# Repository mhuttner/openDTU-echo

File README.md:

# openDTU Echo

PCB for openDTU onBattery

This PCB can be easily ordered from JLCPCB with assembly, but the ESP32-S3 and the Ebyte E49-900M20S module need to be soldered by hand.

## Features

- ESP32-S3
- CMT2300A Chip in an Ebyte E49-900M20S module, NRF Chip is **not** supported
- Three ADUM1201 isolators with Ports for Victron VE.Direct Charge controllers / Smart Shunt
- SN65HVD230 CAN transceiver connected to RJ45 connector (Pin 4 and 5)
- ISL3178EIBZ RS485 transceiver connected to RJ45 connector (Pin 1 and 2)
- 3.3V Switching regulator based on the TPS54202DDC
- I2C Header for an OLED display

## Schematic

## PCB

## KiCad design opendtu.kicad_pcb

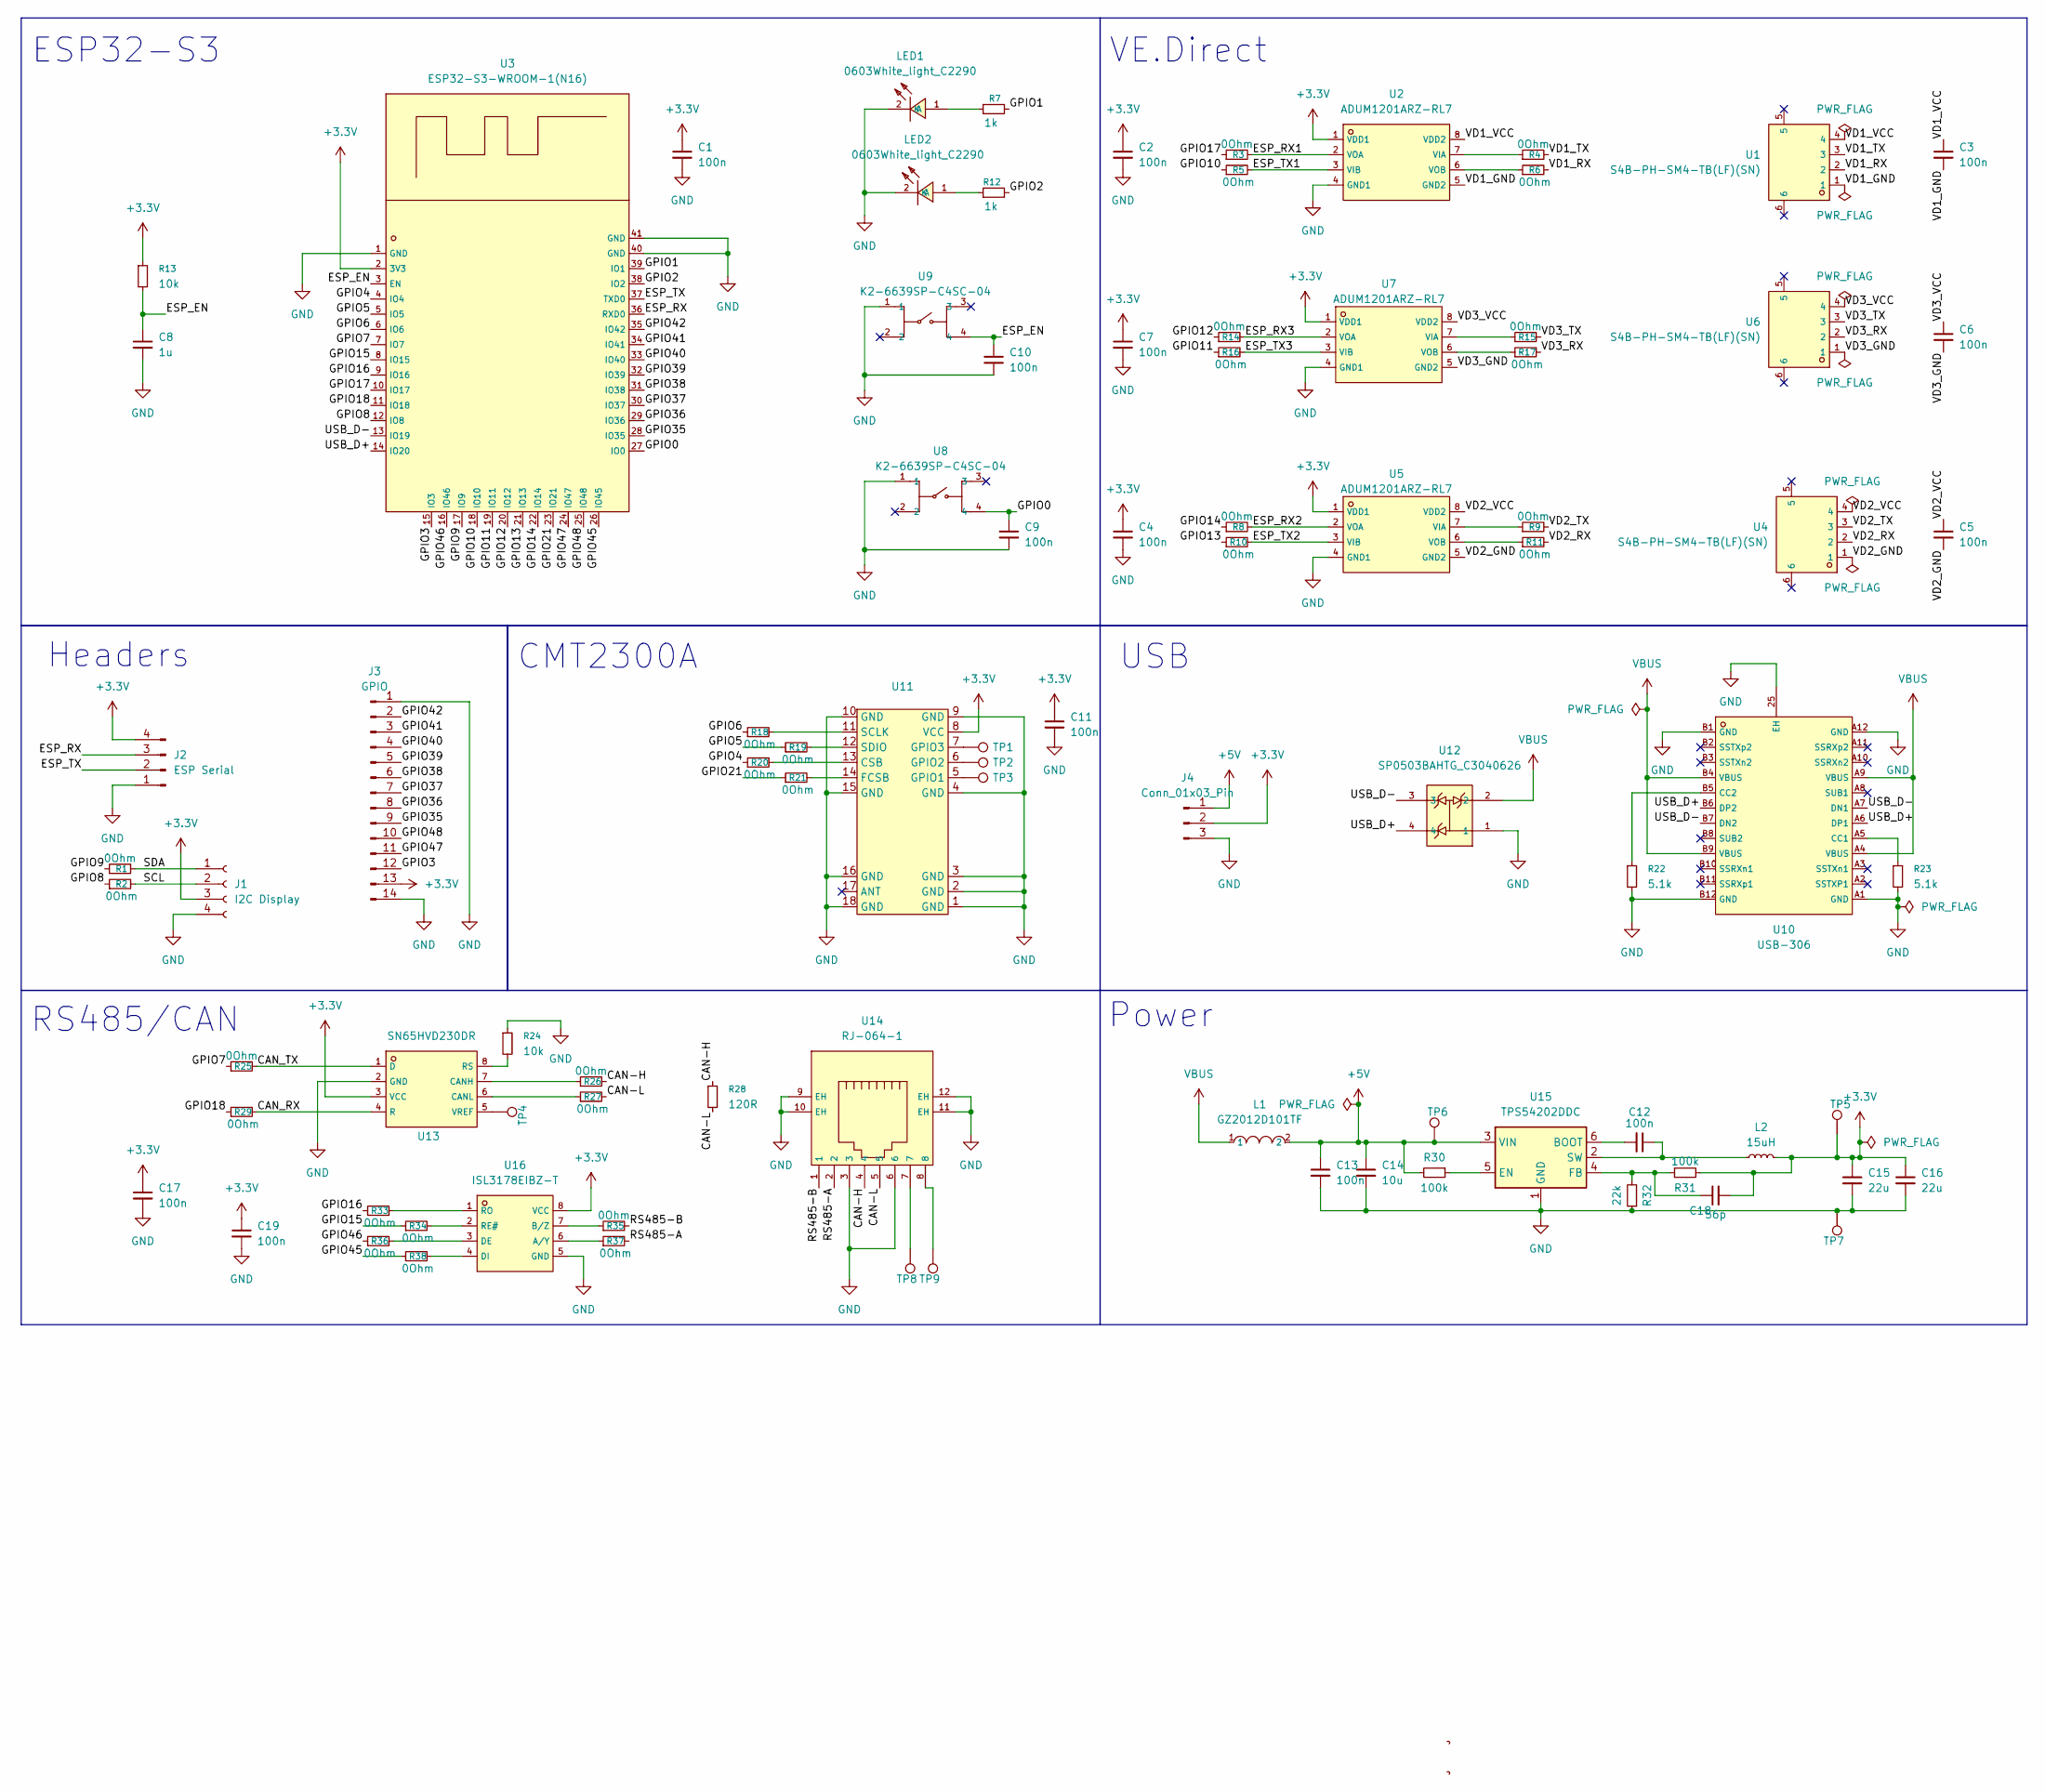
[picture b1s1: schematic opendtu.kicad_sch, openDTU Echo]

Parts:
C1, C2, C3, C4, C5, C6, C7, C9, C10, C11, C12, C17, C19: 100n; C_0402_1005Metric
C8: 1u; C_0603_1608Metric
C13: 100n; C_0603_1608Metric
C14: 10u; C_0603_1608Metric
C15, C16: 22u; C_1206_3216Metric
C18: 56p; C_0603_1608Metric
J1: I2C Display; PinSocket_1x04_P2.54mm_Vertical
J2: ESP Serial; PinHeader_1x04_P2.54mm_Vertical
J3: GPIO; PinHeader_1x14_P2.54mm_Vertical
J4: Conn_01x03_Pin; PinHeader_1x03_P2.54mm_Vertical
L1: GZ2012D101TF; L0805; LCSC C1015
L2: 15uH; IND-SMD_L7.1-W6.6_SLO0618H
LED1, LED2: 0603White_light_C2290; LED0603-R-RD_WHITE; LCSC C2290
R1, R2, R3, R4, R5, R6, R8, R9, R10, R11, R14, R15, R16, R17, R18, R19, R20, R21, R25, R26, R27, R29, R33, R34, R35, R36, R37, R38: 0Ohm; R_0805_2012Metric
R7, R12: 1k; R_0603_1608Metric
R13: 10k; C_0805_2012Metric
R22, R23: 5.1k; R_0805_2012Metric
R24: 10k; R_0805_2012Metric
R28: 120R; R_0805_2012Metric
R30, R31: 100k; R_0805_2012Metric
R32: 22k; R_0805_2012Metric
TP1, TP2, TP3, TP4, TP5, TP6, TP7, TP8, TP9: TestPoint; TestPoint_Pad_D2.0mm
U1, U4, U6: S4B-PH-SM4-TB(LF)(SN); CONN-SMD_S4B-PH-SM4-TB-LF-SN; LCSC C265102
U2, U5, U7: ADUM1201ARZ-RL7; SOIC-8_L4.9-W3.9-P1.27-LS6.0-BL; LCSC C9669
U3: ESP32-S3-WROOM-1(N16); WIRELM-SMD_ESP32-S3-WROOM-1; LCSC C2913199
U8, U9: K2-6639SP-C4SC-04; KEY-SMD_4P-L6.0-W6.0-P3.90-LS9.0; LCSC C83206
U10: USB-306; USB-TYPE-C-TH_USB-306.; LCSC C309338
U11: E49-900M20S
U12: SP0503BAHTG_C3040626; SOT-143-4_L2.9-W1.3-P1.92-LS2.4-BL; LCSC C3040626
U13: SN65HVD230DR; SOIC-8_L4.9-W3.9-P1.27-LS6.0-BL; LCSC C12084
U14: RJ-064-1; CONN-SMD_RJ-064; LCSC C7205199
U15: TPS54202DDC; SOT-23-6
U16: ISL3178EIBZ-T; SOIC-8_L4.9-W3.9-P1.27-LS6.0-BL; LCSC C382015

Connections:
+3.3V: C1.1, C2.1, C4.1, C7.1, C11.1, C15.1, C16.1, C17.1, C18.2, C19.1, J1.3, J2.4, J3.13, J4.2, L2.2, R13.1, R31.2, TP5.1, U2.1 (VDD1), U3.2 (3V3), U5.1 (VDD1), U7.1 (VDD1), U11.8 (VCC), U13.3 (VCC), U16.8 (VCC)
+5V: C13.1, C14.1, J4.1, L1.2, R30.2, TP6.1, U15.3 (VIN)
/CAN-H: R26.2, R28.1, U14.4
/CAN-L: R27.2, R28.2, U14.5
/CAN_RX: R29.2, U13.4 (R)
/CAN_TX: R25.2, U13.1 (D)
/ESP_EN: C8.1, C10.1, R13.2, U3.3 (EN), U9.4
/ESP_RX: J2.3, U3.36 (RXD0)
/ESP_RX1: R3.2, U2.2 (VOA)
/ESP_RX2: R8.2, U5.2 (VOA)
/ESP_RX3: R14.2, U7.2 (VOA)
/ESP_TX: J2.2, U3.37 (TXD0)
/ESP_TX1: R5.2, U2.3 (VIB)
/ESP_TX2: R10.2, U5.3 (VIB)
/ESP_TX3: R16.2, U7.3 (VIB)
/GPIO0: C9.1, U3.27 (IO0), U8.4
/GPIO1: R7.2, U3.39 (IO1)
/GPIO2: R12.2, U3.38 (IO2)
/GPIO3: J3.12, U3.15 (IO3)
/GPIO4: R20.1, U3.4 (IO4)
/GPIO5: R19.1, U3.5 (IO5)
/GPIO6: R18.1, U3.6 (IO6)
/GPIO7: R25.1, U3.7 (IO7)
/GPIO8: R2.1, U3.12 (IO8)
/GPIO9: R1.1, U3.17 (IO9)
/GPIO10: R5.1, U3.18 (IO10)
/GPIO11: R16.1, U3.19 (IO11)
/GPIO12: R14.1, U3.20 (IO12)
/GPIO13: R10.1, U3.21 (IO13)
/GPIO14: R8.1, U3.22 (IO14)
/GPIO15: R34.1, U3.8 (IO15)
/GPIO16: R33.1, U3.9 (IO16)
/GPIO17: R3.1, U3.10 (IO17)
/GPIO18: R29.1, U3.11 (IO18)
/GPIO21: R21.1, U3.23 (IO21)
/GPIO35: J3.9, U3.28 (IO35)
/GPIO36: J3.8, U3.29 (IO36)
/GPIO37: J3.7, U3.30 (IO37)
/GPIO38: J3.6, U3.31 (IO38)
/GPIO39: J3.5, U3.32 (IO39)
/GPIO40: J3.4, U3.33 (IO40)
/GPIO41: J3.3, U3.34 (IO41)
/GPIO42: J3.2, U3.35 (IO42)
/GPIO45: R38.1, U3.26 (IO45)
/GPIO46: R36.1, U3.16 (IO46)
/GPIO47: J3.11, U3.24 (IO47)
/GPIO48: J3.10, U3.25 (IO48)
/RS485-A: R37.2, U14.2
/RS485-B: R35.2, U14.1
/SCL: J1.2, R2.2
/SDA: J1.1, R1.2
/USB_D+: U3.14 (IO20), U10.A6 (DP1), U10.B6 (DP2), U12.4
/USB_D-: U3.13 (IO19), U10.A7 (DN1), U10.B7 (DN2), U12.3
/VD1_GND: C3.2, U1.1, U2.5 (GND2)
/VD1_RX: R6.2, U1.2
/VD1_TX: R4.2, U1.3
/VD1_VCC: C3.1, U1.4, U2.8 (VDD2)
/VD2_GND: C5.2, U4.1, U5.5 (GND2)
/VD2_RX: R11.2, U4.2
/VD2_TX: R9.2, U4.3
/VD2_VCC: C5.1, U4.4, U5.8 (VDD2)
/VD3_GND: C6.2, U6.1, U7.5 (GND2)
/VD3_RX: R17.2, U6.2
/VD3_TX: R15.2, U6.3
/VD3_VCC: C6.1, U6.4, U7.8 (VDD2)
GND: C1.2, C2.2, C4.2, C7.2, C8.2, C9.2, C10.2, C11.2, C13.2, C14.2, C15.2, C16.2, C17.2, C19.2, J1.4, J2.1, J3.1, J3.14, J4.3, LED1.2 (K), LED2.2 (K), R22.2, R23.2, R24.1, R32.1, TP7.1, U2.4 (GND1), U3.1 (GND), U3.40 (GND), U3.41 (GND), U5.4 (GND1), U7.4 (GND1), U8.1, U9.1, U10.25 (EH), U10.A1 (GND), U10.A12 (GND), U10.B1 (GND), U10.B12 (GND), U11.1 (GND), U11.2 (GND), U11.3 (GND), U11.4 (GND), U11.9 (GND), U11.10 (GND), U11.15 (GND), U11.16 (GND), U11.18 (GND), U12.1, U13.2 (GND), U14.3, U14.6, U14.9 (EH), U14.10 (EH), U14.11 (EH), U14.12 (EH), U15.1 (GND), U16.5 (GND)
unnamed: LED1.1 (A), R7.1
unnamed: LED2.1 (A), R12.1
unnamed: TP8.1, U14.7
unnamed: TP9.1, U14.8
unnamed: R4.1, U2.7 (VIA)
unnamed: R6.1, U2.6 (VOB)
unnamed: R9.1, U5.7 (VIA)
unnamed: R11.1, U5.6 (VOB)
unnamed: R15.1, U7.7 (VIA)
unnamed: R17.1, U7.6 (VOB)
unnamed: R23.1, U10.A5 (CC1)
unnamed: R22.1, U10.B5 (CC2)
unnamed: R20.2, U11.13 (CSB)
unnamed: R21.2, U11.14 (FCSB)
unnamed: TP3.1, U11.5 (GPIO1)
unnamed: TP2.1, U11.6 (GPIO2)
unnamed: TP1.1, U11.7 (GPIO3)
unnamed: R18.2, U11.11 (SCLK)
unnamed: R19.2, U11.12 (SDIO)
unnamed: R26.1, U13.7 (CANH)
unnamed: R27.1, U13.6 (CANL)
unnamed: R24.2, U13.8 (RS)
unnamed: TP4.1, U13.5 (VREF)
unnamed: C12.2, U15.6 (BOOT)
unnamed: R30.1, U15.5 (EN)
unnamed: C18.1, R31.1, R32.2, U15.4 (FB)
unnamed: C12.1, L2.1, U15.2 (SW)
unnamed: R37.1, U16.6 (A/Y)
unnamed: R35.1, U16.7 (B/Z)
unnamed: R36.2, U16.3 (DE)
unnamed: R38.2, U16.4 (DI)
unnamed: R34.2, U16.2 (RE#)
unnamed: R33.2, U16.1 (RO)
VBUS: L1.1, U10.A4 (VBUS), U10.A9 (VBUS), U10.B4 (VBUS), U10.B9 (VBUS), U12.2

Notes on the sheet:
ESP32-S3
VE.Direct
Headers
RS485/CAN
CMT2300A
Power
USB

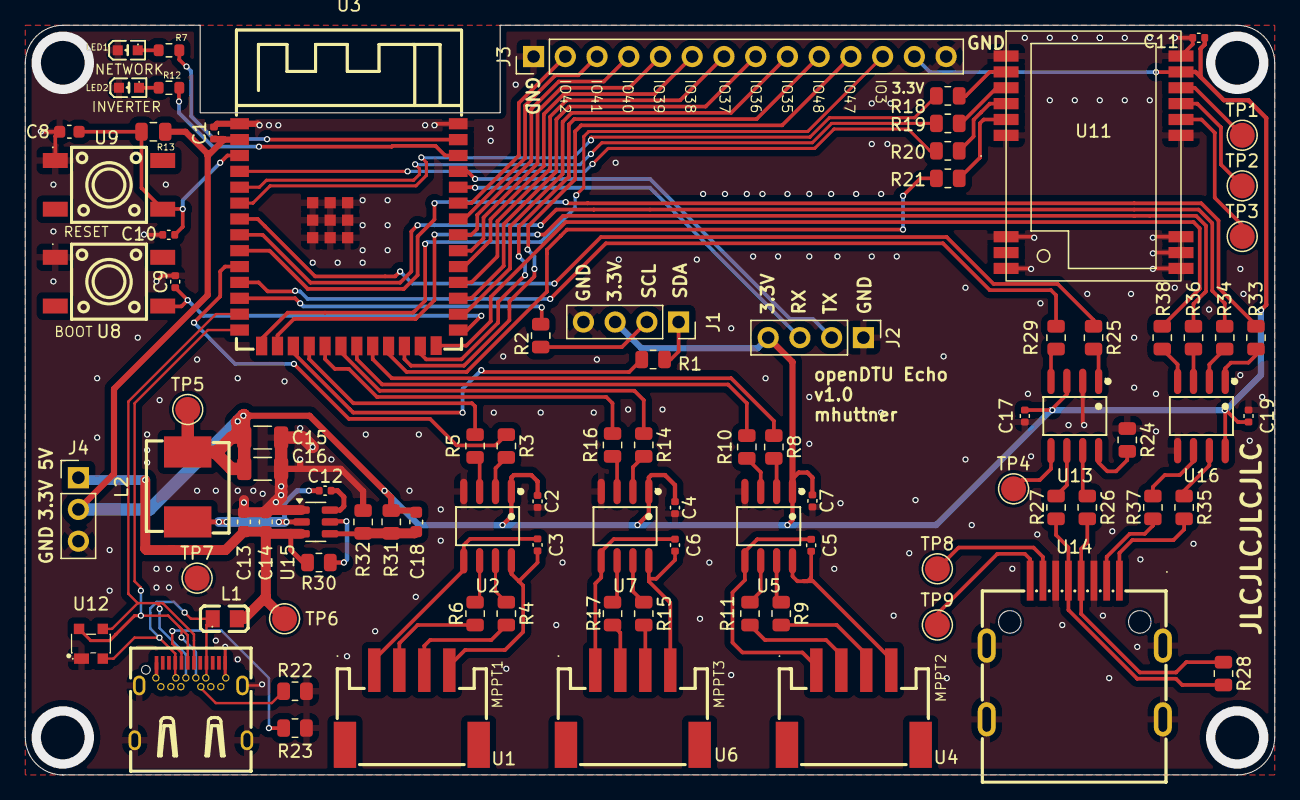
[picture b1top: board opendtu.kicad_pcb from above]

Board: 2 copper layers, 100.0 x 60.0 mm, 90 parts (0 on the bottom side), 100 nets.

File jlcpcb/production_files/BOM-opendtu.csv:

Comment,Designator,Footprint,LCSC,Quantity
GZ2012D101TF,L1,L0805,C1015,1
SN65HVD230DR,U13,SOIC-8_L4.9-W3.9-P1.27-LS6.0-BL,C12084,1
22u,"C15,C16",C_1206_3216Metric,C12891,2
100n,C13,C_0603_1608Metric,C14663,1
100k,"R30,R31",R_0805_2012Metric,C149504,2
100n,"C1,C10,C11,C12,C17,C19,C2,C3,C4,C5,C6,C7,C9",C_0402_1005Metric,C1525,13
1u,C8,C_0603_1608Metric,C15849,1
56p,C18,C_0603_1608Metric,C1676,1
10k,"R13,R24",C_0805_2012Metric,C17414,2
120R,R28,R_0805_2012Metric,C17437,1
0Ohm,"R1,R10,R11,R14,R15,R16,R17,R18,R19,R2,R20,R21,R25,R26,R27,R29,R3,R33,R34,R35,R36,R37,R38,R4,R5,R6,R8,R9",R_0805_2012Metric,C17477,28
22k,R32,R_0805_2012Metric,C17560,1
15uH,L2,IND-SMD_L7.1-W6.6_SLO0618H,C182182,1
10u,C14,C_0603_1608Metric,C19702,1
1k,"R12,R7",R_0603_1608Metric,C21190,2
0603White_light_C2290,"LED1,LED2",LED0603-R-RD_WHITE,C2290,2
S4B-PH-SM4-TB(LF)(SN),"U1,U4,U6",CONN-SMD_S4B-PH-SM4-TB-LF-SN,C265102,3
5.1k,"R22,R23",R_0805_2012Metric,C27834,2
ESP32-S3-WROOM-1(N16),U3,WIRELM-SMD_ESP32-S3-WROOM-1,C2913199,1
SP0503BAHTG_C3040626,U12,SOT-143-4_L2.9-W1.3-P1.92-LS2.4-BL,C3040626,1
USB-306,U10,USB-TYPE-C-TH_USB-306.,C309338,1
ISL3178EIBZ-T,U16,SOIC-8_L4.9-W3.9-P1.27-LS6.0-BL,C382015,1
RJ-064-1,U14,CONN-SMD_RJ-064,C7205199,1
K2-6639SP-C4SC-04,"U8,U9",KEY-SMD_4P-L6.0-W6.0-P3.90-LS9.0,C83206,2
ADUM1201ARZ-RL7,"U2,U5,U7",SOIC-8_L4.9-W3.9-P1.27-LS6.0-BL,C9669,3
TestPoint,TP1,TestPoint_Pad_D2.0mm,,1
TestPoint,TP7,TestPoint_Pad_D2.0mm,,1
TestPoint,TP9,TestPoint_Pad_D2.0mm,,1
ESP Serial,J2,PinHeader_1x04_P2.54mm_Vertical,,1
Conn_01x04_Socket,J1,PinSocket_1x04_P2.54mm_Vertical,,1
TestPoint,TP3,TestPoint_Pad_D2.0mm,,1
Conn_01x14_Pin,J3,PinHeader_1x14_P2.54mm_Vertical,,1
~,U11,E49-900M20S,,1
TestPoint,TP6,TestPoint_Pad_D2.0mm,,1
Conn_01x03_Pin,J4,PinHeader_1x03_P2.54mm_Vertical,,1
TestPoint,TP2,TestPoint_Pad_D2.0mm,,1
TestPoint,TP4,TestPoint_Pad_D2.0mm,,1
TestPoint,TP5,TestPoint_Pad_D2.0mm,,1
TPS54202DDC,U15,SOT-23-6,,1
TestPoint,TP8,TestPoint_Pad_D2.0mm,,1

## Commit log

2025-05-14 add readme
2025-05-14 add images
2025-05-14 fix image
2025-05-14 docs
2025-05-14 update jlcpcb
